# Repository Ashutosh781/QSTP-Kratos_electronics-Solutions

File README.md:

# QSTP-Kratos_electronics-Solutions

This is a solution repository for [adbidwai/QSTP-Kratos_electronics](https://github.com/adbidwai/QSTP-Kratos_electronics)

Each week has its detailed separate README files with all the information

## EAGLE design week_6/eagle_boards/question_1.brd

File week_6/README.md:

##PLEASE READ THIS FILE FOR INSTRUCTIONS OF HOW TO OPEN AND USE THE CREATED PROGRAMS AND DESCRIPTION OF THOSE PROGRAMS##

##PLEASE INFORM ME IF ANYTHING IS NOT WORKING##

#THE SCHEMATICS ARE MADE IN EAGLE v8.2.2#

#EXTRA LIBRARIES NEEDED FOR SCHEMATICS TO OPEN ARE AS FOLLOWS#

1)  ADAFRUIT

    https://github.com/adafruit/Adafruit-Eagle-Library

    FOLLOW THE INSTRUCTIONS TO ADD THE LIBRARY TO THE USE IN EAGLE FOR ALL THE LIBRARIES

2)  SPARKFUN

    https://github.com/sparkfun/SparkFun-Eagle-Libraries

    CLONE THIS GITHUB REPO

3)  LM2596.lbr

    https://www.diymodules.org/eagle

    USE THE FIRST DOWNLOAD LINK IN THE PAGE

4)  XT60-M.lbr

    https://www.snapeda.com/parts/XT60-M/AMASS/view-part/2883912/

5)  IRFZ44N.lbr

    https://www.snapeda.com/parts/IRFZ44N/Infineon%20Technologies/view-part/

#OPEN THE eagle_boards PROJECT IN EAGLE

#EACH QUESTION SEPARATE SCHEMATIC (.sch files) AND BOARD (.brd files) ARE MADE INSIDE THE SAME PROJECT#

#TRACE WIDTH CALCULATION IS DONE USING THE FOLLOWING LINK BY TAKING VALUES GIVEN IN THE QUESTIONS PDF

https://www.digikey.com/en/resources/conversion-calculators/conversion-calculator-pcb-trace-width

#TO FABRICATE THE BOARD GERBER FILES CAN EASILY BE GENERATED FROM THE BOARDS

##-----------------------------------------------------------------------------------------------------------------##

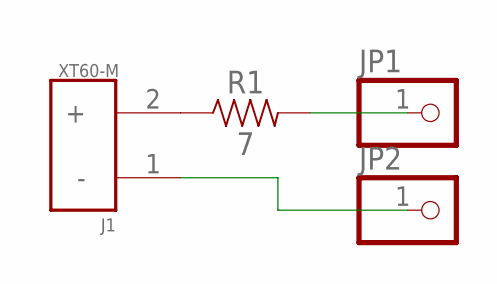
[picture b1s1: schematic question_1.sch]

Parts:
J1: XT60-M; AMASS_XT60-M
JP1, JP2: PINHD-1X1; 1X01
R1: 7; 0603

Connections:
unnamed: J1.2 (+), R1.1
unnamed: JP1.1, R1.2
unnamed: J1.1 (-), JP2.1

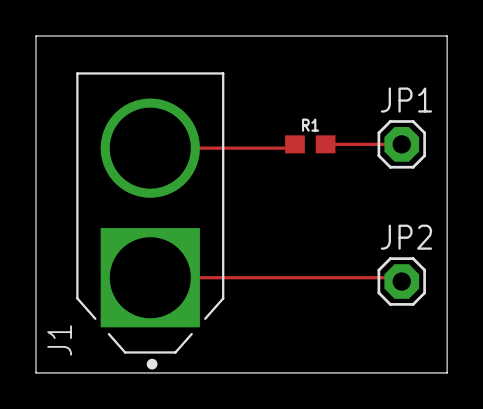
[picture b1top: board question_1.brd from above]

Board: 2 copper layers, 22.8 x 18.7 mm, 4 parts (0 on the bottom side), 3 nets.

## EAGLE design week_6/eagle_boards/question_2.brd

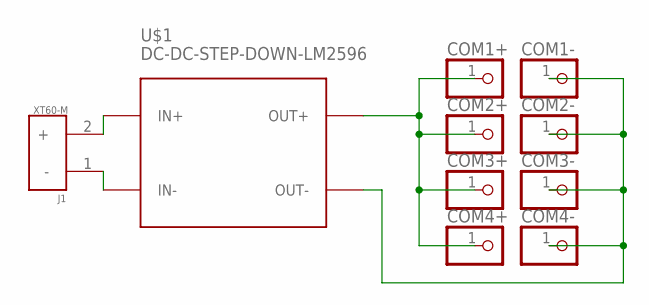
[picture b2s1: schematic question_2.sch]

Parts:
COM1+, COM1-, COM2+, COM2-, COM3+, COM3-, COM4+, COM4-: PINHD-1X1; 1X01
J1: XT60-M; AMASS_XT60-M
U$1: DC-DC-STEP-DOWN-LM2596

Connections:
unnamed: J1.1 (-), U$1.IN-
unnamed: J1.2 (+), U$1.IN+
unnamed: COM1+.1, COM2+.1, COM3+.1, COM4+.1, U$1.OUT+
unnamed: COM1-.1, COM2-.1, COM3-.1, COM4-.1, U$1.OUT-

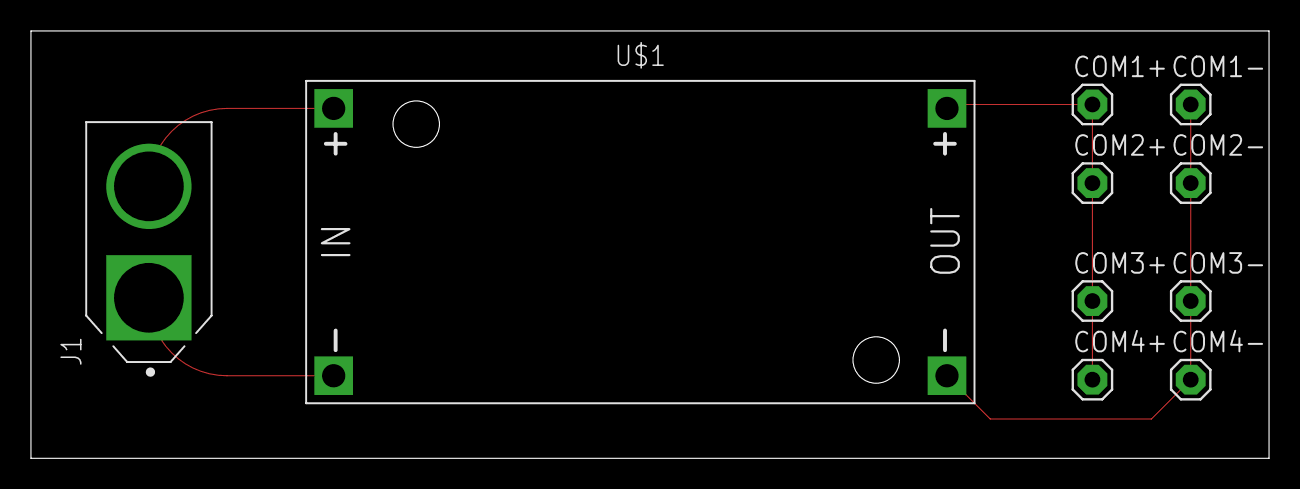
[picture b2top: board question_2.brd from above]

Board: 2 copper layers, 80.0 x 27.6 mm, 10 parts (0 on the bottom side), 4 nets.

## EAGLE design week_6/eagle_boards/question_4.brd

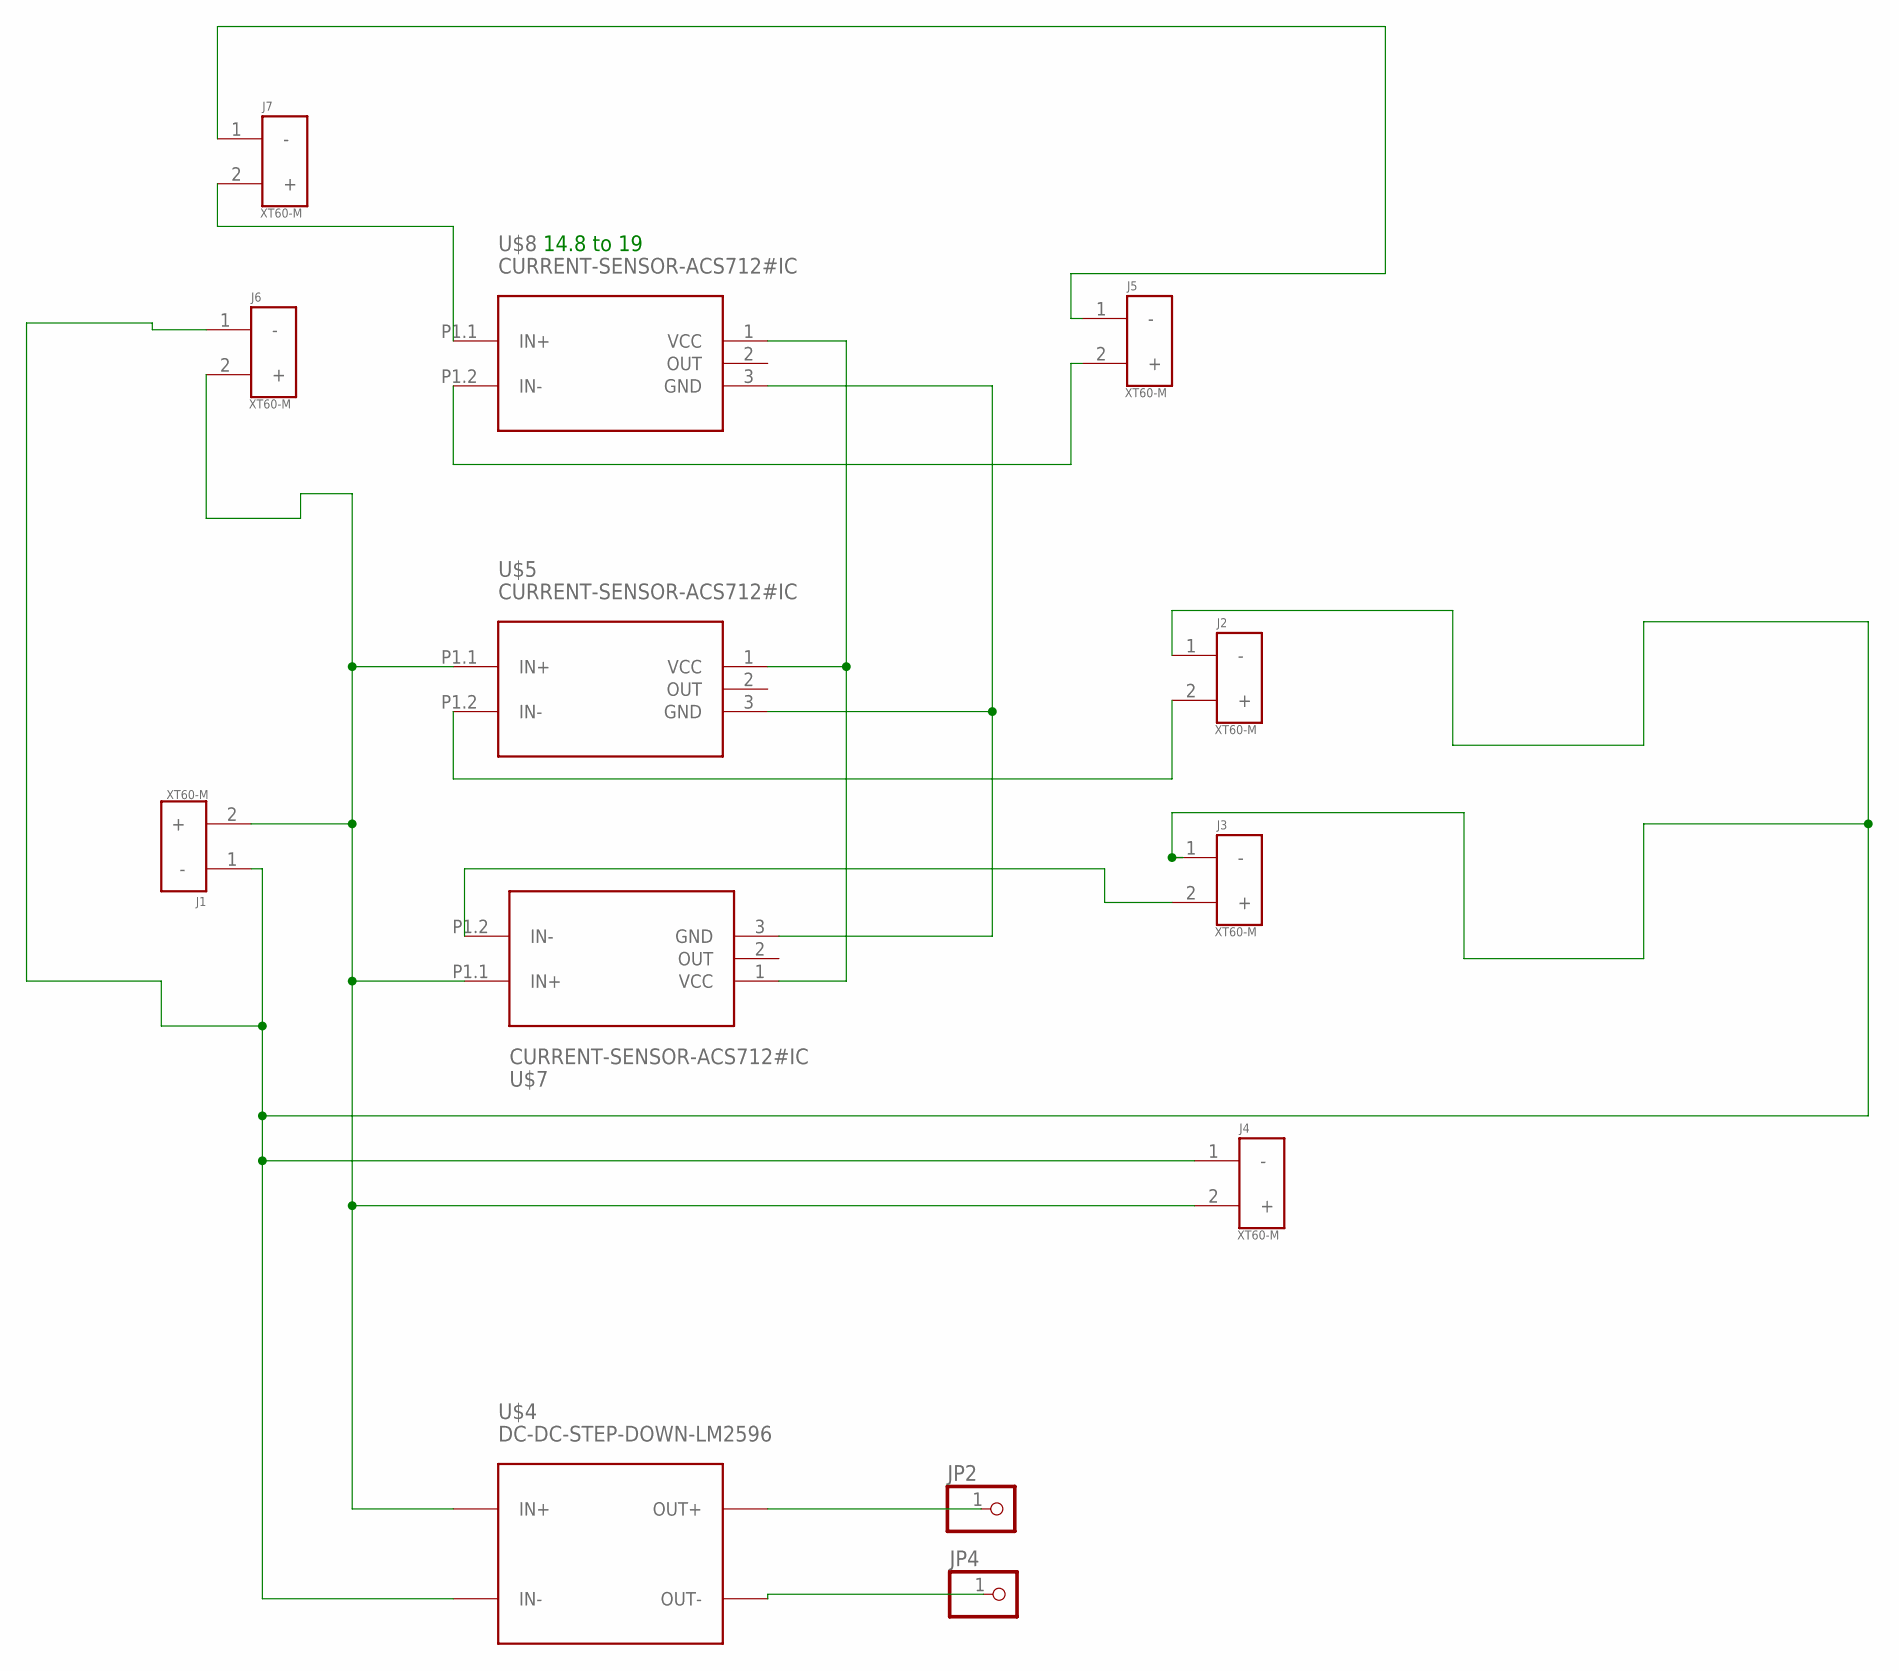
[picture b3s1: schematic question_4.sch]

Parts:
J1, J2, J3, J4, J5, J6, J7: XT60-M; AMASS_XT60-M
JP2, JP4: PINHD-1X1; 1X01
U$4: DC-DC-STEP-DOWN-LM2596
U$5, U$7, U$8: CURRENT-SENSOR-ACS712#IC

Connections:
unnamed: J7.2 (+), U$8.P1.1 (IN+)
unnamed: J1.1 (-), J2.1 (-), J3.1 (-), J4.1 (-), J6.1 (-), U$4.IN-
unnamed: J5.1 (-), J7.1 (-)
unnamed: J1.2 (+), J4.2 (+), J6.2 (+), U$4.IN+, U$5.P1.1 (IN+), U$7.P1.1 (IN+)
unnamed: J2.2 (+), U$5.P1.2 (IN-)
unnamed: JP4.1, U$4.OUT-
unnamed: J3.2 (+), U$7.P1.2 (IN-)
unnamed: J5.2 (+), U$8.P1.2 (IN-)
unnamed: JP2.1, U$4.OUT+
unnamed: U$5.1 (VCC), U$7.1 (VCC), U$8.1 (VCC)
unnamed: U$5.3 (GND), U$7.3 (GND), U$8.3 (GND)

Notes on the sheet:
14.8 to 19

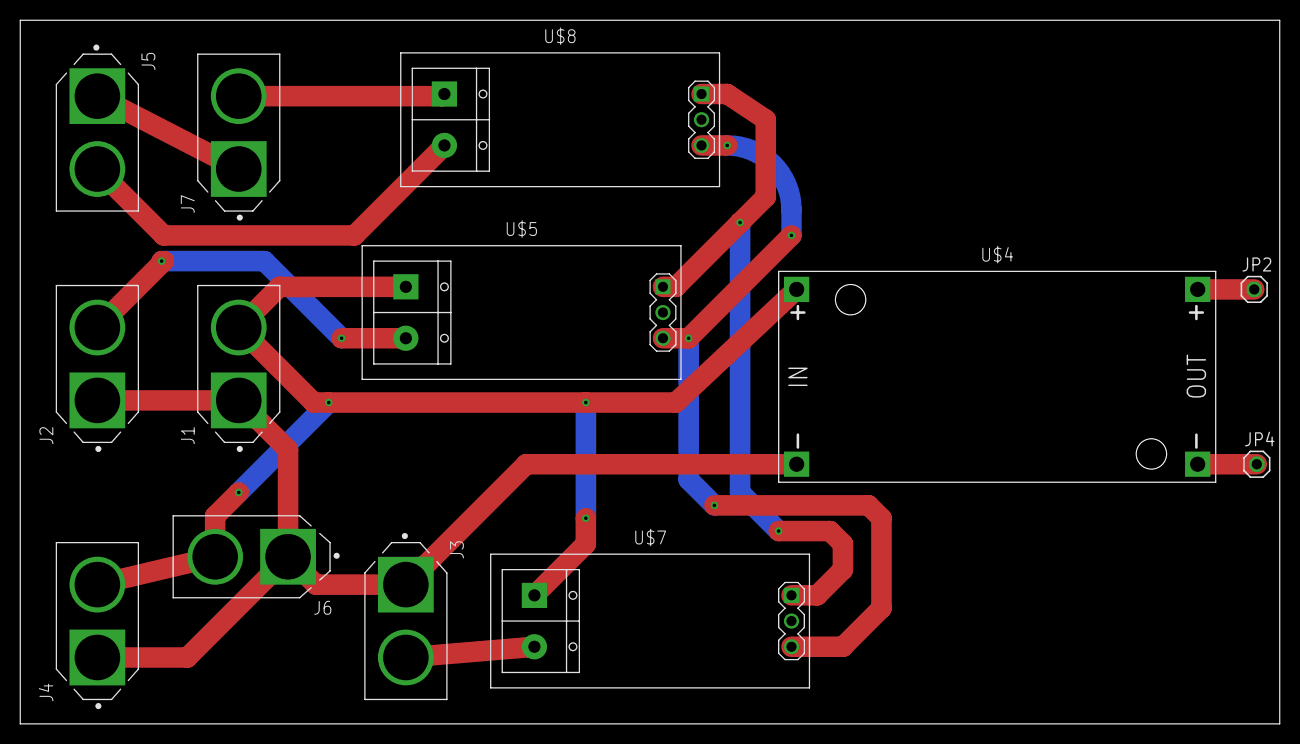
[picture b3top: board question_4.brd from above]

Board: 2 copper layers, 124.4 x 69.5 mm, 13 parts (0 on the bottom side), 11 nets.

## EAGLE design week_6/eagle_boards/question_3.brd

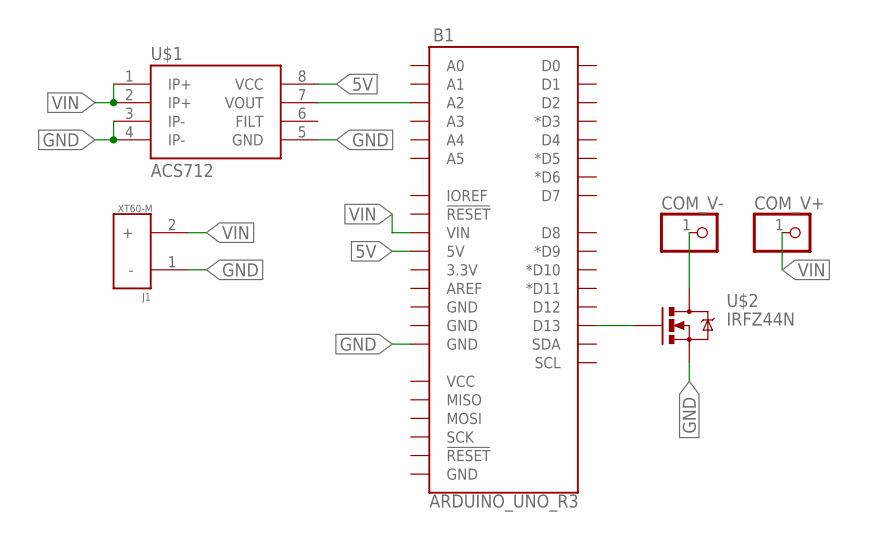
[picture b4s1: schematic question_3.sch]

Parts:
B1: ARDUINO_UNO_R3; ARDUINO_R3
COM_V+: PINHD-1X1; 1X01
COM_V-: PINHD-1X1; 1X01
J1: XT60-M; AMASS_XT60-M
U$1: ACS712; SO08
U$2: IRFZ44N; TO-220

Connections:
5V: B1.5V, U$1.8 (VCC)
GND: B1.GND@2 (GND), J1.1 (-), U$1.3 (IP-), U$1.4 (IP-), U$1.5 (GND), U$2.3 (S)
unnamed: B1.D13, U$2.1 (G)
unnamed: COM_V-.1, U$2.2 (D)
unnamed: B1.A2, U$1.7 (VOUT)
VIN: B1.VIN, COM_V+.1, J1.2 (+), U$1.1 (IP+), U$1.2 (IP+)

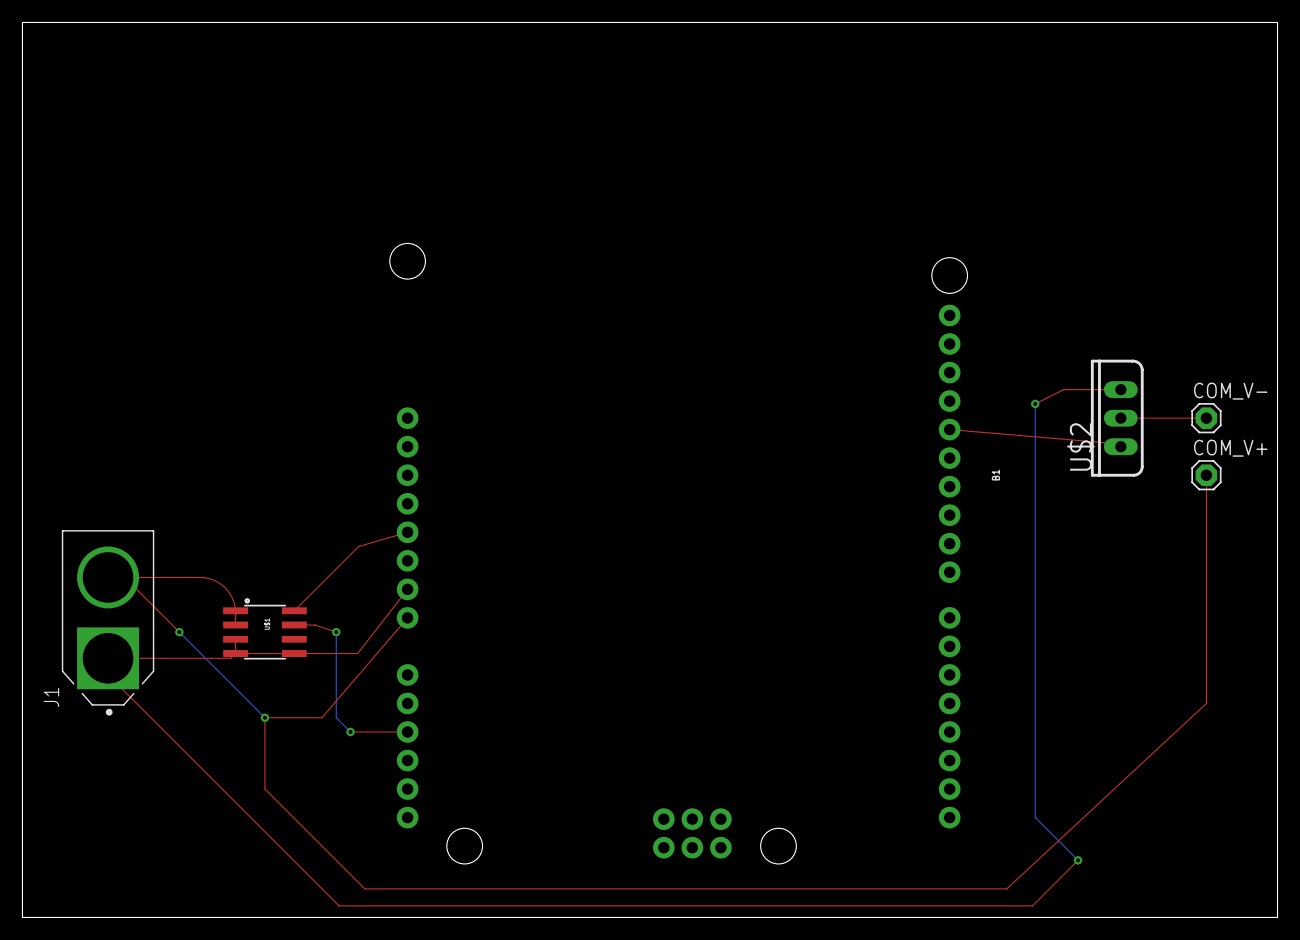
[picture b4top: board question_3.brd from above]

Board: 2 copper layers, 111.7 x 79.7 mm, 6 parts (0 on the bottom side), 6 nets.

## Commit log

2020-05-18 Rename readme.md to README.md

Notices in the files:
parts and their libraries:
SparkFun-Resistors: Licensing: Creative Commons ShareAlike 4.0 International - https://creativecommons.org/licenses/by-sa/4.0
lm2596: Released under the Creative Commons Attribution 4.0 International License: http://creativecommons.org/licenses/by/4.0
